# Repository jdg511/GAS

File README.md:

# The Great American Spring

JUCE 7 audio effect by Illicit Apothecary.

Release v2.5 defines the GAS fork from the former Stereo Crossfeed Convolver project. It packages only the four final spring tank IR files:

- `GBS-L.wav`
- `GBS-R.wav`
- `GAS-L.wav`
- `GAS-R.wav`

The plugin provides Main Tanks, optional Ext Reverb Tanks in series or parallel, a constant-sum stereo crossfade, FilterClipper, feedback phase control, mono source handling, and wet/dry output mixing.

## Hardware Mapping Notes

For the real device, the simulation's `predelay + convolution IR` stage should be treated as the software stand-in for a physical spring reverb tank.

- Primary tank simulation: both channels represent `4AB1C1B` tanks.
- Secondary tank simulation: left channel represents a `9EB2C1B` tank and right channel represents a `9EB3C1B` tank.

This means the current JUCE simulation is not just a generic convolution reverb. Its timing and IR choices are standing in for the mechanical behavior of the spring tanks we intend to use in hardware.
Only the predelay and convolution portions are simulation-only. They exist to emulate the behavior of the real spring tanks; the rest of the signal path should be treated as candidate hardware behavior unless we explicitly decide otherwise later.

## Hardware Platform Constraints

The real-world unit should be designed as primarily analog hardware:

- Use passive components, solid-state transistors, and analog / mixed-signal ICs as the main building blocks.
- Do not base the PCB design on an MCU, Arduino, Raspberry Pi, or other general-purpose embedded computer.
- The production hardware should replace the simulation-only predelay and convolution stages with real spring tanks and supporting analog electronics, not runtime convolution or software processing on the PCB.

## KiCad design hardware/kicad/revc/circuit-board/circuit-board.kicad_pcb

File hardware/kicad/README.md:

# KiCad Workspace

KiCad 10 is installed locally on this machine.

This folder is the intended home for the hardware project once schematic capture starts.

## Planned Contents

- `GAS-Hardware.kicad_pro`
- `GAS-Hardware.kicad_sch`
- one schematic file scaffold per board
- board layouts for:
  - input-output
  - tank-driver-recovery
  - ext-tank-routing
  - crossfade-feedback-wet-summing
  - filter-clipper

## Current Status

The KiCad project now has a **real top-level hierarchical shell**, first-pass real symbol capture across every rev-A child sheet, and a first-pass electrically assigned power/backplane page.

What currently exists:

- file naming
- top-level sheet ownership and page ordering
- title blocks
- top-level system notes
- child-sheet interface labels for global rails, I/O boundary nets, inter-board audio nets, and frozen control nets
- first-pass symbol population on every rev-A board sheet
- first-pass DC-entry, rail-generation, and harness-fanout net assignment on `power-backplane.kicad_sch`
- PCB placement scaffold files for all six rev-A boards, generated from the documented board envelope assumptions
- DRC-clean placement scaffolds with four M3 mounting holes plus all currently assigned schematic footprints per board
- capture sequencing
- validated CLI export workflow
- a manifest-driven audit script for measuring schematic population progress

What does **not** yet exist:

- real inter-sheet and intra-sheet pin-level wiring on the five audio/control sheets
- clean ERC after the new symbol-only capture phase
- finished footprint assignment inside every schematic page
- routed copper, zones, final component placement, or Gerber/drill fabrication exports for the PCB files

Capture should now key off:

- [rev-a-schematic-packets.md](C:/Users/Jason/GAS-build/repo/hardware/rev-a-schematic-packets.md:1)
- [rev-a-electrical-capture-worksheet.md](C:/Users/Jason/GAS-build/repo/hardware/rev-a-electrical-capture-worksheet.md:1)
- [rev-a-io-schematic-ready-definition.md](C:/Users/Jason/GAS-build/repo/hardware/rev-a-io-schematic-ready-definition.md:1)
- [rev-a-ext-routing-schematic-ready-definition.md](C:/Users/Jason/GAS-build/repo/hardware/rev-a-ext-routing-schematic-ready-definition.md:1)
- [rev-a-tank-driver-recovery-schematic-ready-definition.md](C:/Users/Jason/GAS-build/repo/hardware/rev-a-tank-driver-recovery-schematic-ready-definition.md:1)
- [rev-a-crossfade-feedback-wet-schematic-ready-definition.md](C:/Users/Jason/GAS-build/repo/hardware/rev-a-crossfade-feedback-wet-schematic-ready-definition.md:1)
- [rev-a-filter-clipper-schematic-ready-definition.md](C:/Users/Jason/GAS-build/repo/hardware/rev-a-filter-clipper-schematic-ready-definition.md:1)
- [rev-a-control-backplane-schematic-ready-definition.md](C:/Users/Jason/GAS-build/repo/hardware/rev-a-control-backplane-schematic-ready-definition.md:1)
- [rev-a-interconnect-pin-map.md](C:/Users/Jason/GAS-build/repo/hardware/rev-a-interconnect-pin-map.md:1)
- [rev-a-bringup-sequence.md](C:/Users/Jason/GAS-build/repo/hardware/rev-a-bringup-sequence.md:1)
- [rev-a-sheet-population-plan.md](C:/Users/Jason/GAS-build/repo/hardware/kicad/rev-a-sheet-population-plan.md:1)
- [rev-a-symbol-manifest.csv](C:/Users/Jason/GAS-build/repo/hardware/kicad/rev-a-symbol-manifest.csv:1)
- [rev-a-net-label-manifest.csv](C:/Users/Jason/GAS-build/repo/hardware/kicad/rev-a-net-label-manifest.csv:1)

## Verification

During this session, the hierarchical top-level shell and all child sheets were accepted by `kicad-cli`, and the release-export script still produced schematic PDFs successfully after the interface-label pass.

Important current nuance:

- symbol population is intentionally ahead of real wire placement
- `kicad-cli sch export pdf` still succeeds
- top-level ERC is no longer clean at this intermediate stage because the hierarchical labels are not yet attached to real wires or symbols
- the current ERC result is therefore a **known intermediate failure**, not a claim that the capture is electrically complete

Current exported folder:

- the historical placeholder export artifact still exists as a file named `hardware/kicad/exports`

Repeatable release/export helper:

- [export-rev-a-release.ps1](C:/Users/Jason/GAS-build/repo/hardware/kicad/export-rev-a-release.ps1:1)
- [rev-a-release-manifest.csv](C:/Users/Jason/GAS-build/repo/hardware/kicad/rev-a-release-manifest.csv:1)

Repeatable capture-progress audit:

- [audit-rev-a-capture.py](C:/Users/Jason/GAS-build/repo/hardware/kicad/audit-rev-a-capture.py:1)
- [rev-a-capture-audit.md](C:/Users/Jason/GAS-build/repo/hardware/kicad/rev-a-capture-audit.md:1)

Run:

```powershell
python hardware/kicad/audit-rev-a-capture.py
```

Current baseline from the latest `2026-06-29` audit:

- top-level hierarchy: `6 / 6` child sheets present
- populated schematic refs: `88 / 88`
- explicit manifest net labels: `82 / 82`

Current release-export / ERC baseline from the same session:

- capture audit: `88 / 88` planned refs present and `82 / 82` manifest labels present
- top-level ERC: `650` known intermediate violations after the I/O-board center-short cleanup pass on `2026-06-29`
- the I/O child sheet dropped from `404` to `376` local violations in the same pass, and its multiple-net-name collisions dropped from `8` to `2`
- the remaining I/O multiple-net-name warnings are the intentional `WD_L_LO <-> WET_SUM_L` and `WD_R_LO <-> WET_SUM_R` wet-return aliases
- the remaining ERC debt is still dominated by top-level unconnected sheet pins, placeholder wire endpoints, off-grid legacy symbol endpoints, and still-unwired child-sheet labels on the non-power sheets
- the power/backplane page itself still stands as the most electrically assigned sheet, but it is not yet the final ripple-decoupling or chassis-bond implementation

Current PCB scaffold baseline:

- `crossfade-feedback-wet.kicad_pcb`: `100 mm x 70 mm`, 8 electrical footprints, 4x M3 mounting holes, DRC clean
- `ext-tank-routing.kicad_pcb`: `120 mm x 80 mm`, 12 electrical footprints, 4x M3 mounting holes, DRC clean
- `filter-clipper.kicad_pcb`: `140 mm x 90 mm`, 19 electrical footprints, 4x M3 mounting holes, DRC clean
- `io-board.kicad_pcb`: `160 mm x 75 mm`, 50 electrical footprints, 4x M3 mounting holes, DRC clean
- `power-backplane.kicad_pcb`: `150 mm x 95 mm`, 14 electrical footprints, 4x M3 mounting holes, DRC clean
- `tank-driver-recovery.kicad_pcb`: `170 mm x 110 mm`, 11 electrical footprints, 4x M3 mounting holes, DRC clean
- these are **placement scaffolds only** and are not routed fabrication outputs

Repeatable PCB footprint placement helper:

- [place-rev-a-board-footprints.py](C:/Users/Jason/GAS-build/repo/hardware/kicad/place-rev-a-board-footprints.py:1)

Current scripted output root:

- `hardware/kicad/release-exports/rev-a-release`

## Order Readiness Gate

Before ordering boards, run:

```powershell
.\hardware\kicad\test-rev-a-order-readiness.ps1
```

The gate writes:

- [rev-a-order-readiness.md](C:/Users/Jason/GAS-build/repo/hardware/kicad/rev-a-order-readiness.md:1)
- [GAS-Hardware-erc-current.json](C:/Users/Jason/GAS-build/repo/hardware/kicad/GAS-Hardware-erc-current.json:1)

It intentionally fails while any of these are true:

- no `*.kicad_pcb` board layout files exist
- top-level ERC has violations
- non-virtual schematic symbols have empty footprint fields
- KiCad/SPICE simulation model properties are absent

The current project is therefore **not order-ready**. It remains in schematic-capture cleanup before PCB layout, DRC, Gerber/drill export, and simulation setup.

## Planned Export Set

- fabrication Gerbers
- drill files
- schematic PDFs
- `BOM.csv`
- centroid / position files
- assembly drawings
- bring-up and calibration notes

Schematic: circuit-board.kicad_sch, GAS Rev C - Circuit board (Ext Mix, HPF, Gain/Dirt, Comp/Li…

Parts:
C101, C103, C105, C207, C208, C209, C210, C307, C308, C309, C310, C805, C1201, C1202, C1241, C1303, C1304, C1305, C1306, C1307, C1308, C1323, C1324, C1345, C1346: 100nF; C_0603_1608Metric; MPN CL10B104KB8NNNC
C102, C110, C111: 10uF 25V; CP_Elec_5x5.8; MPN UWT1E100MCL1GB
C104: 47uF 16V; CP_Elec_6.3x7.7; MPN EEE-FK1C470P
C201, C211, C220, C301, C311, C320, C1302, C1322: 22pF; C_0603_1608Metric; MPN CL10C220JB8NNNC
C202, C203, C212, C213, C302, C303, C312, C313: 68nF film; C_1210_3225Metric; MPN ECH-U1H683JX5
C204, C214, C304, C314: 15nF film; C_1206_3216Metric; MPN ECH-U1H153JX5
C205, C215, C305, C315: 6.8nF film; C_0805_2012Metric; MPN ECH-U1H682JX5
C801, C804, C901, C904, C1301, C1321, C1341, C1342, C1344: 1uF film; C_Rect_L7.2mm_W4.5mm_P5.00mm_FKS2_FKP2_MKS2_MKP2; MPN MKS2C041001F00KSSD
C803, C903: 51pF; C_0603_1608Metric; MPN CL10C510JB8NNNC
C1343: 100pF; C_0603_1608Metric; MPN CL10C101JB8NNNC
D1F, D2F, D3F, D4F, D5F, D801, D802, D901, D902, D1241, D1242, D1341, D1342, D1343: 1N4148W; D_SOD-123; MPN 1N4148W-7-F
D1243: 1N5819HW; D_SOD-123; MPN 1N5819HW-7-F
H1, H2, H3, H4: M3; MountingHole_3.2mm_M3_Pad_Via
K1, K2, K3, K4, K5: G6K-2F-Y DC5; Relay_DPDT_Omron_G6K-2F-Y; MPN G6K-2F-Y DC5
P1: TANK-RET (from tank board); JST_XH_B6B-XH-A_1x06_P2.50mm_Vertical; MPN B6B-XH-A(LF)(SN)
P2: WET-OUT (to io-board); JST_XH_B3B-XH-A_1x03_P2.50mm_Vertical; MPN B3B-XH-A(LF)(SN)
P3: FB-RET (to tank board); JST_XH_B3B-XH-A_1x03_P2.50mm_Vertical; MPN B3B-XH-A(LF)(SN)
P4: PWR (from power board); JST_VH_B4P-VH_1x04_P3.96mm_Vertical; MPN B4P-VH(LF)(SN)
P5: CTL-A: HPF quad 50k lin (PTD904-2015K-B503) on it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; JST_XH_B8B-XH-A_1x08_P2.50mm_Vertical; MPN B8B-XH-A(LF)(SN)
P6: CTL-B: LPF quad 50k lin (PTD904-2015K-B503) on it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; JST_XH_B8B-XH-A_1x08_P2.50mm_Vertical; MPN B8B-XH-A(LF)(SN)
P7: CTL-C: Ext Mix dual 10k lin, Feedback dual 10k lin; JST_XH_B12B-XH-A_1x12_P2.50mm_Vertical; MPN B12B-XH-A(LF)(SN)
P8: CTL-D: switch lines (from control deck); JST_XH_B7B-XH-A_1x07_P2.50mm_Vertical; MPN B7B-XH-A(LF)(SN)
P9: CTL-E: Gain dual 10k lin (control deck P4); JST_XH_B6B-XH-A_1x06_P2.50mm_Vertical; MPN B6B-XH-A(LF)(SN)
Q1201, Q1221: MMBF5457; SOT-23; MPN MMBF5457
Q1341: MMBT3906; SOT-23; MPN MMBT3906-7-F
R60, R61, R62, R63, R64, R101, R102, R207, R213, R236, R307, R313, R336, R1208, R1228, R1244, R1245, R1343, R1344, R1345, R1346, R1348, R1351, R1357: 10k; R_0603_1608Metric; MPN RC0603FR-0710KL
R201, R202, R301, R302: 1.43k; R_0603_1608Metric; MPN RC0603FR-071K43L
R203, R208, R234, R303, R308, R334, R1203, R1204, R1223, R1224: 1M; R_0603_1608Metric; MPN RC0603FR-071ML
R204, R205, R209, R210, R304, R305, R309, R310: 499R; R_0603_1608Metric; MPN RC0603FR-07499RL
R206, R306: 5.9k; R_0603_1608Metric; MPN RC0603FR-075K9L
R211, R220, R221, R222, R223, R224, R311, R320, R321, R322, R323, R324, R801, R804, R901, R904, R1206, R1207, R1226, R1227, R1350, R1353, R1355, R1356: 100k; R_0603_1608Metric; MPN RC0603FR-07100KL
R212, R312: 15.8k; R_0603_1608Metric; MPN RC0603FR-0715K8L
R214, R230, R233, R314, R330, R333: 100R; R_0603_1608Metric; MPN RC0603FR-07100RL
R215, R315, R1205, R1225: 47k; R_0603_1608Metric; MPN RC0603FR-0747KL
R216, R316: 680R; R_0603_1608Metric; MPN RC0603FR-07680RL
R231, R232, R331, R332, R1241, R1242, R1301, R1302, R1303, R1304, R1321, R1322, R1323, R1324, R1341, R1342, R1347, R1349: 20k; R_0603_1608Metric; MPN RC0603FR-0720KL
R235, R335: 59k; R_0603_1608Metric; MPN RC0603FR-0759KL
R802, R902: 4.7k; R_0603_1608Metric; MPN RC0603FR-074K7L
R803, R903: 51k; R_0603_1608Metric; MPN RC0603FR-0751KL
R1201, R1221: 22k; R_0603_1608Metric; MPN RC0603FR-0722KL
R1202, R1222: 2.2k; R_0603_1608Metric; MPN RC0603FR-072K2L
R1243: 40.2k; R_0603_1608Metric; MPN RC0603FR-0740K2L
R1246: 1.5k; R_0603_1608Metric; MPN RC0603FR-071K5L
R1247: 2.2M; R_0603_1608Metric; MPN RC0603FR-072M2L
R1305, R1325: 150k; R_0603_1608Metric; MPN RC0603FR-07150KL
R1306, R1326: 5.1k; R_0603_1608Metric; MPN RC0603FR-075K1L
R1352: 182k; R_0603_1608Metric; MPN RC0603FR-07182KL
R1354: 1.82M; R_0603_1608Metric; MPN RC0603FR-071M82L
RV1201, RV1221, RV1342: 10k; Potentiometer_Bourns_3314J_Vertical; MPN 3314J-1-103E
RV1301, RV1321: 50k; Potentiometer_Bourns_3314J_Vertical; MPN 3314J-1-503E
U101: L78L09; SOT-89-3; MPN L78L09ACUTR
U102, U402: TL072HIDR; SOIC-8_3.9x4.9mm_P1.27mm; MPN TL072HIDR
U201, U202, U301, U302, U1201, U1301, U1302, U1305: OPA1679IDR; SOIC-14_3.9x8.7mm_P1.27mm; MPN OPA1679IDR
U1303, U1304: V2181; SIP-8_19x3mm_P2.54mm; MPN V2181

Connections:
+5VAUX: P4.4, P8.6
+9VC: C102.1, C103.1, C105.1, C805.1, R101.1, U101.1 (OUT), U102.8 (V+), U402.8 (V+)
+15VA: C101.1, C110.1, C207.1, C209.1, C307.1, C309.1, C1201.1, C1303.1, C1305.1, C1307.1, C1323.1, C1345.1, P4.1, R1355.1, RV1301.1, RV1321.1, U101.3 (IN), U201.4 (V+), U202.4 (V+), U301.4 (V+), U302.4 (V+), U1201.4 (V+), U1301.4 (V+), U1302.4 (V+), U1303.7 (V+), U1304.7 (V+), U1305.4 (V+)
-15VA: C111.2, C208.2, C210.2, C308.2, C310.2, C1202.2, C1304.2, C1306.2, C1308.2, C1324.2, C1346.2, P4.3, R1306.2, R1326.2, R1356.2, RV1201.1, RV1221.1, RV1301.3, RV1321.3, U201.11 (V-), U202.11 (V-), U301.11 (V-), U302.11 (V-), U1201.11 (V-), U1301.11 (V-), U1302.11 (V-), U1305.11 (V-)
AGND: C101.2, C102.2, C103.2, C104.2, C105.2, C110.2, C111.1, C205.2, C207.2, C208.1, C209.2, C210.1, C215.2, C305.2, C307.2, C308.1, C309.2, C310.1, C315.2, C805.2, C1201.2, C1202.1, C1241.2, C1303.2, C1304.1, C1305.2, C1306.1, C1307.2, C1308.1, C1323.2, C1324.1, C1344.2, C1345.2, C1346.1, D1F.2 (A), D2F.2 (A), D3F.2 (A), D4F.2 (A), D5F.2 (A), H1.1, H2.1, H3.1, H4.1, K1.8, K2.8, K3.8, K4.8, K5.8, P1.2, P1.5, P2.2, P3.2, P4.2, P5.3, P5.7, P7.3, P7.6, P7.9, P7.12, P8.7, Q1201.2 (S), Q1221.2 (S), Q1341.1 (B), R60.2, R61.2, R62.2, R63.2, R64.2, R102.2, R207.2, R208.2, R211.2, R216.2, R223.2, R224.2, R234.2, R236.2, R307.2, R308.2, R311.2, R316.2, R323.2, R324.2, R334.2, R336.2, R804.2, R904.2, R1202.2, R1208.2, R1222.2, R1228.2, R1247.2, R1352.2, R1357.2, RV1201.3, RV1221.3, U101.2 (GND), U102.4 (V-), U102.5 (+), U201.3 (+), U201.10 (+), U202.3 (+), U202.12 (+), U301.3 (+), U301.10 (+), U302.3 (+), U302.12 (+), U402.4 (V-), U1201.10 (+), U1201.12 (+), U1301.3 (+), U1301.5 (+), U1301.10 (+), U1301.12 (+), U1303.2 (EC+), U1303.6 (GND), U1304.2 (EC+), U1304.6 (GND), U1305.3 (+), U1305.5 (+), U1305.10 (+), U1305.12 (+)
BUS_L: K3.3, R209.1, R211.1
BUS_R: K3.6, R309.1, R311.1
CL_OP: D1341.2 (A), U1302.7
CTL_COMP: D2F.1 (K), K2.1, P8.2, R61.1
CTL_DIRT: D1F.1 (K), K1.1, P8.1, R60.1
CTL_FB_INV: D4F.1 (K), K4.1, P8.5, R63.1
CTL_LIMIT: D3F.1 (K), K3.1, P8.3, R62.1
CTL_MEGA: D5F.1 (K), K5.1, P8.4, R64.1
DET_AVG: C1344.1, R1346.2, R1350.1
DET_C_L: C1341.2, R1341.1
DET_C_R: C1342.2, R1342.1
DET_OUT: C1343.2, Q1341.2 (E), R1351.1, U1305.14
DET_SUM: R1343.2, R1344.1, R1347.1, U1305.1
DET_SUM_N: R1341.2, R1342.2, R1343.1, U1305.2 (-)
DYN_IN_L: K1.3, K2.2, R1201.1, R1301.1
DYN_IN_R: K1.6, K2.7, R1221.1, R1321.1
DYN_MID_L: K2.3, K3.2
DYN_MID_R: K2.6, K3.7
EXM_L_W: P7.2, R221.1
EXM_R_W: P7.5, R321.1
FBI_N_L: R231.2, R232.1, U202.13 (-)
FBI_N_R: R331.2, R332.1, U302.13 (-)
FBP_L_W: P7.8, R234.1, U202.10 (+)
FBP_R_W: P7.11, R334.1, U302.10 (+)
FB_BUF_L: K4.2, R231.1, U202.8, U202.9 (-)
FB_BUF_R: K4.7, R331.1, U302.8, U302.9 (-)
FB_INV_L: K4.4, R232.2, U202.14
FB_INV_R: K4.5, R332.2, U302.14
FB_RAW_L: K5.3, R233.1
FB_RAW_R: K5.6, R333.1
FB_RET_L: P3.1, R233.2
FB_RET_R: P3.3, R333.2
FB_SEL_L: K4.3, K5.2, K5.5
FB_SEL_R: K4.6, K5.4, K5.7
FET_BIAS_L: R1205.2, RV1201.2
FET_BIAS_R: R1225.2, RV1221.2
FET_CV_L: R1203.2, R1205.1, R1206.1
FET_CV_R: R1223.2, R1225.1, R1226.1
FET_DIV_L: Q1201.1 (D), R1201.2, R1202.1, R1204.2, U1201.3 (+)
FET_DIV_R: Q1221.1 (D), R1221.2, R1222.1, R1224.2, U1201.5 (+)
FET_G_L: Q1201.3 (G), R1203.1, R1204.1
FET_G_R: Q1221.3 (G), R1223.1, R1224.1
FET_MK_L: R1207.2, R1208.1, U1201.2 (-)
FET_MK_R: R1227.2, R1228.1, U1201.6 (-)
FET_OUT_L: K2.4, R1207.1, R1241.1, U1201.1
FET_OUT_R: K2.5, R1227.1, R1242.1, U1201.7
FET_SC: R1206.2, R1226.2, U1302.8, U1302.9 (-)
FW_N: R1347.2, R1348.2, R1349.1, U1305.9 (-)
FW_OUT: R1346.1, R1349.2, U1305.8
GAIN_L_HI: P9.1, R201.2
GAIN_L_LO: P9.3, R202.1
GAIN_L_W: C201.1, P9.2, R203.1, U201.9 (-)
GAIN_OUT_L: C201.2, K1.2, R202.2, R203.2, R215.1, U201.8
GAIN_OUT_R: C301.2, K1.7, R302.2, R303.2, R315.1, U301.8
GAIN_R_HI: P9.4, R301.2
GAIN_R_LO: P9.6, R302.1
GAIN_R_W: C301.1, P9.5, R303.1, U301.9 (-)
HPF_FB_L: R206.2, R207.1, U201.6 (-)
HPF_FB_R: R306.2, R307.1, U301.6 (-)
HPF_L1_W: P5.2, R204.2
HPF_L2_W: P5.4, R205.2
HPF_N1_L: C202.2, C203.1, C212.2, C213.1, R204.1
HPF_N1_R: C302.2, C303.1, C312.2, C313.1, R304.1
HPF_OUT_L: P5.1, R201.1, R206.1, U201.7
HPF_OUT_R: P5.5, R301.1, R306.1, U301.7
HPF_P_L: C203.2, C213.2, R205.1, R208.1, U201.5 (+)
HPF_P_R: C303.2, C313.2, R305.1, R308.1, U301.5 (+)
HPF_R1_W: P5.6, R304.2
HPF_R2_W: P5.8, R305.2
HW_N: D1342.2 (A), R1344.2, R1345.2, U1305.6 (-)
HW_OP: D1342.1 (K), D1343.2 (A), U1305.7
HW_X: D1343.1 (K), R1345.1, R1348.1
LOG_N: C1343.1, Q1341.3 (C), R1350.2, U1305.13 (-)
LPF_L1_W: P6.2, R209.2
LPF_L2_W: P6.4, R210.2
LPF_N1_L: C204.1, C214.1, P6.1, R210.1
LPF_N1_R: C304.1, C314.1, P6.5, R310.1
LPF_OUT_L: C204.2, C214.2, R212.1, U201.13 (-), U201.14
LPF_OUT_R: C304.2, C314.2, R312.1, U301.13 (-), U301.14
LPF_P_L: C205.1, C215.1, P6.3, U201.12 (+)
LPF_P_R: C305.1, C315.1, P6.7, U301.12 (+)
LPF_R1_W: P6.6, R309.2
LPF_R2_W: P6.8, R310.2
MIX_N_L: C220.1, R220.2, R221.2, R222.1, U201.2 (-)
MIX_N_R: C320.1, R320.2, R321.2, R322.1, U301.2 (-)
OB_N_L: C211.1, R212.2, R213.1, U202.2 (-)
OB_N_R: C311.1, R312.2, R313.1, U302.2 (-)
PAD_L: C801.1, R215.2, R216.1
PAD_R: C901.1, R315.2, R316.1
PRI_RET_L: P1.1, R220.1, R223.1
PRI_RET_R: P1.3, R320.1, R323.1
SC2_ENV: C1241.1, R1246.2, R1247.1, U1302.10 (+)
SC2_N: R1241.2, R1242.2, R1243.1, U1201.9 (-)
SC2_OP: D1241.1 (K), D1242.2 (A), U1201.14
SC2_PK: D1243.1 (K), R1246.1
SC2_RN: D1241.2 (A), R1244.2, R1245.2, U1201.13 (-)
SC2_SUM: R1243.2, R1244.1, U1201.8
SC2_X: D1242.1 (K), D1243.2 (A), R1245.1
SEC_BUF_L: P7.1, R230.2
SEC_BUF_R: P7.4, R330.2
SEC_RET_L: P1.4, R224.1, R230.1
SEC_RET_R: P1.6, R324.1, R330.1
SPARE_U102_2: U102.6 (-), U102.7
TANK_MIX_L: C202.1, C212.1, C220.2, R222.2, U201.1
TANK_MIX_R: C302.1, C312.1, C320.2, R322.2, U301.1
TH_BOT: R1356.1, RV1342.3
TH_N: R1353.2, R1354.1, U1302.2 (-)
TH_OUT: R1354.2, U1302.1, U1302.5 (+)
TH_P: R1351.2, R1352.1, U1302.3 (+)
TH_REF: R1353.1, RV1342.2
TH_TOP: R1355.2, RV1342.1
TS_CLIP_L: C803.1, C804.1, D801.1 (K), D802.2 (A), R803.1, U402.1
TS_CLIP_R: C903.1, C904.1, D901.1 (K), D902.2 (A), R903.1, U402.7
TS_DIV_L: C804.2, R804.1, U202.5 (+)
TS_DIV_R: C904.2, R904.1, U302.5 (+)
TS_FB2_L: R235.2, R236.1, U202.6 (-)
TS_FB2_R: R335.2, R336.1, U302.6 (-)
TS_FB_L: C803.2, D801.2 (A), D802.1 (K), R802.1, R803.2, U402.2 (-)
TS_FB_R: C903.2, D901.2 (A), D902.1 (K), R902.1, R903.2, U402.6 (-)
TS_IN_L: C801.2, R801.1, U402.3 (+)
TS_IN_R: C901.2, R901.1, U402.5 (+)
TS_OUT_L: K1.4, R235.1, U202.7
TS_OUT_R: K1.5, R335.1, U302.7
VBIAS: R801.2, R802.2, R901.2, R902.2, U102.1, U102.2 (-)
VB_RAW: C104.1, R101.2, R102.1, U102.3 (+)
VCA_C_L: C1301.2, R1303.1
VCA_C_R: C1321.2, R1323.1
VCA_EC: U1302.13 (-), U1302.14, U1303.3 (EC-), U1304.3 (EC-)
VCA_EC_RAW: D1341.1 (K), R1357.1, U1302.6 (-), U1302.12 (+)
VCA_INV_L: C1301.1, R1302.2, U1301.1
VCA_INV_R: C1321.1, R1322.2, U1301.8
VCA_IN_L: R1303.2, U1303.1 (IN)
VCA_IN_N_L: R1301.2, R1302.1, U1301.2 (-)
VCA_IN_N_R: R1321.2, R1322.1, U1301.9 (-)
VCA_IN_R: R1323.2, U1304.1 (IN)
VCA_OUT_L: C1302.2, C1341.1, K3.4, R1304.2, U1301.7
VCA_OUT_R: C1322.2, C1342.1, K3.5, R1324.2, U1301.14
VCA_O_L: C1302.1, R1304.1, U1301.6 (-), U1303.8 (OUT)
VCA_O_R: C1322.1, R1324.1, U1301.13 (-), U1304.8 (OUT)
VCA_SYMW_L: R1305.1, RV1301.2
VCA_SYMW_R: R1325.1, RV1321.2
VCA_SYM_L: R1305.2, U1303.4 (SYM)
VCA_SYM_R: R1325.2, U1304.4 (SYM)
VCA_VN_L: R1306.1, U1303.5 (V-/ISET)
VCA_VN_R: R1326.1, U1304.5 (V-/ISET)
WET_L: P2.1, R214.2
WET_R: P2.3, R314.2
WET_RAW_L: C211.2, P7.7, R213.2, R214.1, U202.1
WET_RAW_R: C311.2, P7.10, R313.2, R314.1, U302.1

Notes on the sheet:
Connectors
Mechanical
Power, +9VC, VBIAS
Main path L: Ext Mix sum, HPF, Gain, LPF
Output, feedback, make-ups L
Tube Screamer L: Rf 51k / Rg 4.7k, 1N4148W pair, +9VC
Main path R: Ext Mix sum, HPF, Gain, LPF
Output, feedback, make-ups R
Tube Screamer R: Rf 51k / Rg 4.7k, 1N4148W pair, +9VC
Comp: MMBF5457 FET compressor (1176 territory), linked feedback sidechain
Limit: Coolaudio V2181 VCA x2 (THAT 2181 pin-compatible), discrete log-average detector (feedback), 10:1
Limit detector + threshold
Relays: Dirt, Comp, Limit, FB phase, MEGAVERB (Omron G6K-2F-Y 5 V)
Power flags

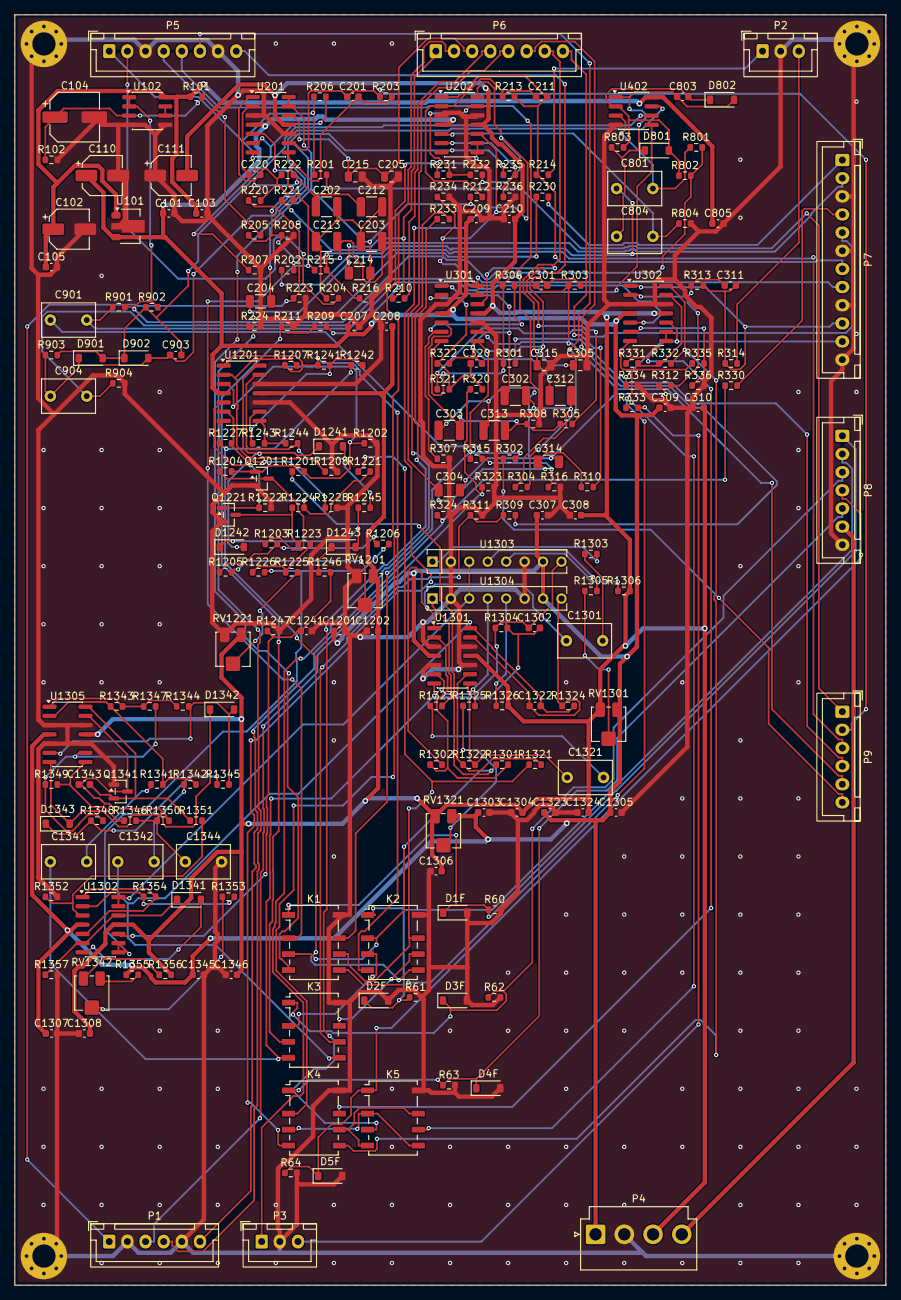
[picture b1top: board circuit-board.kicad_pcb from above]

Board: 2 copper layers, 120.0 x 175.0 mm, 242 parts (0 on the bottom side), 154 nets.

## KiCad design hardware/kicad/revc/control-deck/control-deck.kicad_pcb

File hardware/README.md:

# GAS Hardware Build

This folder is the starting point for turning the JUCE spring-reverb simulation into a real analog product.

## Core Constraints

- The real unit is primarily analog.
- Use passive parts, transistors, and analog or mixed-signal ICs.
- Do not use an MCU, Arduino, Raspberry Pi, or other general-purpose embedded computer on the production PCB.
- The external audio interfaces should be balanced line level, nominally `+4 dBu`, with 600-ohm capable line I/O behavior.
- The external audio connectors should be combo `XLR / TRS` jacks.
- The enclosure format is now a **user-supplied cylindrical tube**, `10 in` nominal diameter (standard pipe/cap size; `9 in` fits but is rarely stocked) and about `48 in` long.
- All external audio connections and DC power entry should land on **one circular service endcap**, in the spirit of the original Great British Spring.
- In the audio path, avoid ceramic, tantalum, and electrolytic capacitors wherever practical; prefer film-based or other non-ceramic/non-electrolytic solutions and use direct coupling where it makes sense. Power-supply and rail-decoupling positions may use ceramics or electrolytics when practical.
- Only the simulation's predelay and convolution blocks are software-only stand-ins for the real spring tanks.
- The real hardware should use the target tanks directly:
  - Primary tanks: `4AB1C1B` left and `4AB1C1B` right
  - Secondary tanks: `9EB2C1B` left and `9EB3C1B` right
- Plan around `+15VA / -15VA`, but prefer parts that can tolerate at least `+18V / -18V` wherever practical.
- Mains conversion lives in an **external `+24 VDC` wall-adapter strategy** (`750 mA / 18 W`, Triad Magnetics `WSU240-0750` regulated SMPS from DigiKey, selected `2026-07-04`). The chassis takes DC at a barrel jack and generates `+15V / -15V / +5V` on-board from that single DC input. No mains-side circuitry inside the enclosure. The Triad unit is a regulated SMPS; the P-0 receiving check in [rev-a-external-dc-power.md](rev-a-external-dc-power.md) still applies at first power-up.

## Board Roadmap

We are partitioning the product into analog boards so each section can be designed, tested, and revised independently.

1. Input / Output board
   - Balanced line receiver, dry split, final wet/dry summing, balanced line driver
2. Ext Reverb Tanks Off / Series / Parallel board
   - Secondary tank routing and amount control
3. Filter and Clipping board
   - Drive, HPF, selectable clipping, LPF
4. Tank Driver / Recovery board
   - Real spring tank send and return electronics for primary and secondary tanks
5. Crossfade / Feedback / Mixer board
   - Stereo tank crossfade, feedback loop, phase invert, inter-board summing
6. Power / Control / Interconnect board
   - Analog supply rails, panel controls, board-to-board headers, grounding strategy

## Signal-Path Mapping

The current software path is:

`input -> dry tap + wet path -> tank model -> stereo crossfade -> filter/clipper -> feedback -> wet/dry mix -> output`

The real hardware path should become:

`balanced line receiver -> dry split + wet send -> real tank drive/recovery path -> stereo crossfade -> filter/clipper -> feedback loop -> wet/dry output mixer -> balanced line driver`

The only direct substitution is:

- `predelay + convolution` in software
- replaced by
- real tank drive + real spring tank + recovery stages in hardware

## Design Intent

- Keep the board architecture modular so a third-party PCB house can fabricate repeatable revisions.
- Favor through-hole panel hardware and serviceable connectors where practical.
- Keep the control surface directly analog whenever possible: pots, toggles, rotary switches, relay logic, and analog switch ICs are all acceptable paths.
- Avoid any hardware decision that depends on firmware existing later.

## Build Handoff Entry Points

If you are picking this package up to actually build a unit, start here:

- [rev-a-external-dc-power.md](rev-a-external-dc-power.md) — external wall-adapter power topology and on-board ±15V / +5V generation
- [rev-a-pipe-enclosure-concept.md](rev-a-pipe-enclosure-concept.md) — cylindrical shell, endcap, rail, and tank-mount concept
- [rev-a-endcap-panel-layout.md](rev-a-endcap-panel-layout.md) — service-endcap zoning for combo jacks, DC jack, and controls
- [rev-a-endcap-hole-table.md](rev-a-endcap-hole-table.md) — first drilling/cutout draft for the circular service endcap
- [rev-a-endcap-hole-table.csv](rev-a-endcap-hole-table.csv) — machine-readable companion to the endcap hole table
- [rev-a-board-outline-assumptions.md](rev-a-board-outline-assumptions.md) — target board envelopes and axial placement inside the tube
- [rev-a-board-outline-assumptions.csv](rev-a-board-outline-assumptions.csv) — machine-readable board envelope and station map
- [rev-a-harness-cut-lengths.md](rev-a-harness-cut-lengths.md) — prototype harness cut lengths for boards, tanks, and panel wiring
- [rev-a-harness-cut-lengths.csv](rev-a-harness-cut-lengths.csv) — machine-readable harness-length companion
- [rev-a-board-package-freeze.md](rev-a-board-package-freeze.md) — compact board-by-board freeze for schematic capture and quoting
- [rev-a-electrical-capture-worksheet.md](rev-a-electrical-capture-worksheet.md) — next-pass electrical wiring brief keyed to the actual KiCad refs
- [rev-a-io-schematic-ready-definition.md](rev-a-io-schematic-ready-definition.md) — exact first-pass I/O unit allocation, passive map, and connector/net ownership
- [rev-a-ext-routing-schematic-ready-definition.md](rev-a-ext-routing-schematic-ready-definition.md) — exact first-pass ext-routing relay ownership, control decode, and passive map
- [rev-a-tank-driver-recovery-schematic-ready-definition.md](rev-a-tank-driver-recovery-schematic-ready-definition.md) — exact first-pass tank send/recovery stage ownership, shield strategy, and passive map
- [rev-a-crossfade-feedback-wet-schematic-ready-definition.md](rev-a-crossfade-feedback-wet-schematic-ready-definition.md) — exact first-pass crossfade, wet-return, and feedback-path definition
- [rev-a-filter-clipper-schematic-ready-definition.md](rev-a-filter-clipper-schematic-ready-definition.md) — exact first-pass filter/drive/clip stage ownership and mode truth
- [rev-a-control-backplane-schematic-ready-definition.md](rev-a-control-backplane-schematic-ready-definition.md) — exact first-pass control landing, mode encoding, and backplane reserve policy
- [rev-a-board-connector-schedule.csv](rev-a-board-connector-schedule.csv) — machine-readable connector ownership and harness schedule
- [rev-a-quote-request-packet.md](rev-a-quote-request-packet.md) — exactly which files to send each vendor and template request emails
- [rev-a-total-cost-rollup.md](rev-a-total-cost-rollup.md) — single per-unit cost estimate across electronics, fab, assembly, tanks, enclosure, and labor
- [rev-a-bench-test-procedures.md](rev-a-bench-test-procedures.md) — per-board test procedures with specific signals, equipment, and pass/fail thresholds
- [rev-a-manufacturing.md](rev-a-manufacturing.md) — vendor recommendations and file conventions
- [bom/rev-a-procurement-snapshot.md](bom/rev-a-procurement-snapshot.md) — current exact-part sourcing snapshot and scope split
- [rev-a-bringup-sequence.md](rev-a-bringup-sequence.md) — board-by-board power-up order
- [rev-a-open-issues.md](rev-a-open-issues.md) — what is still genuinely unresolved

## Next Deliverables

- Shared signal naming and connector conventions
- One spec per board
- Schematic packets with stage ownership and pin-level harness maps
- Control-law and circuit-value tables that track the current plugin behavior
- Remaining audio-sheet pin-level

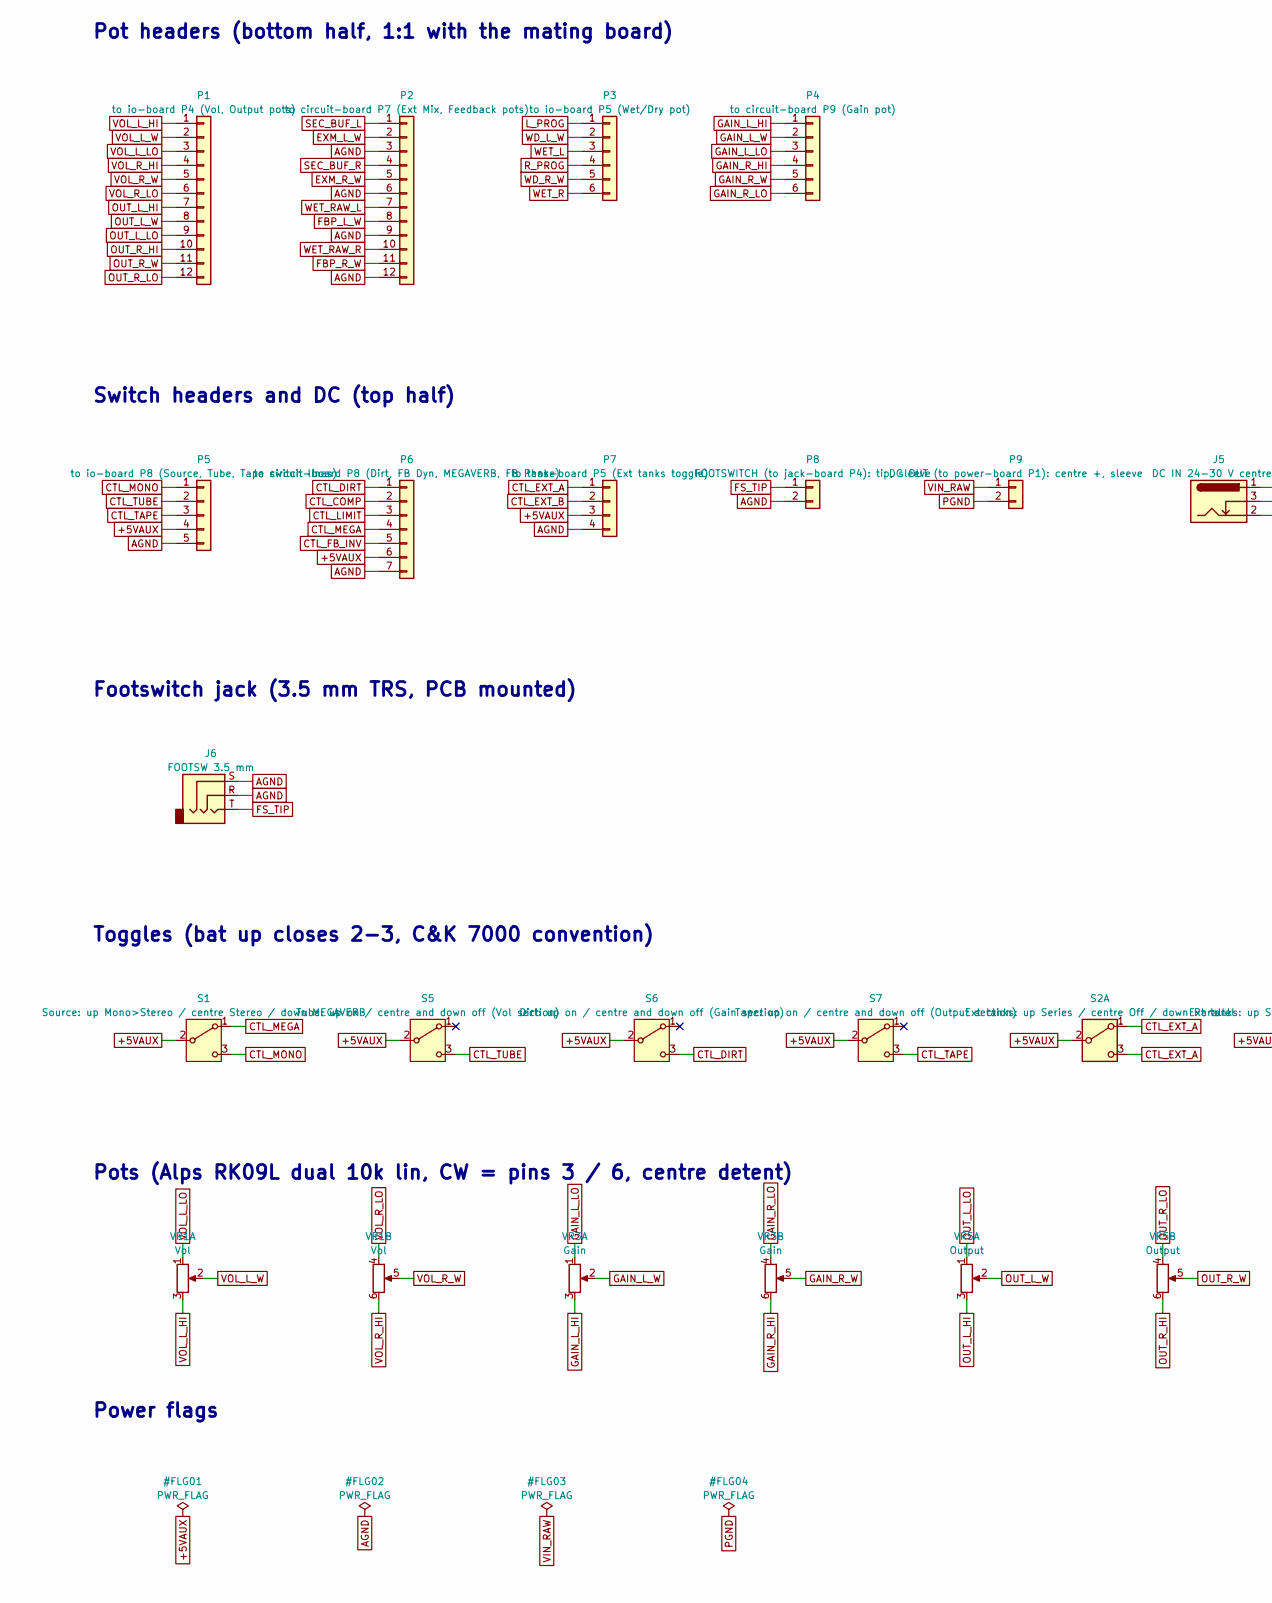
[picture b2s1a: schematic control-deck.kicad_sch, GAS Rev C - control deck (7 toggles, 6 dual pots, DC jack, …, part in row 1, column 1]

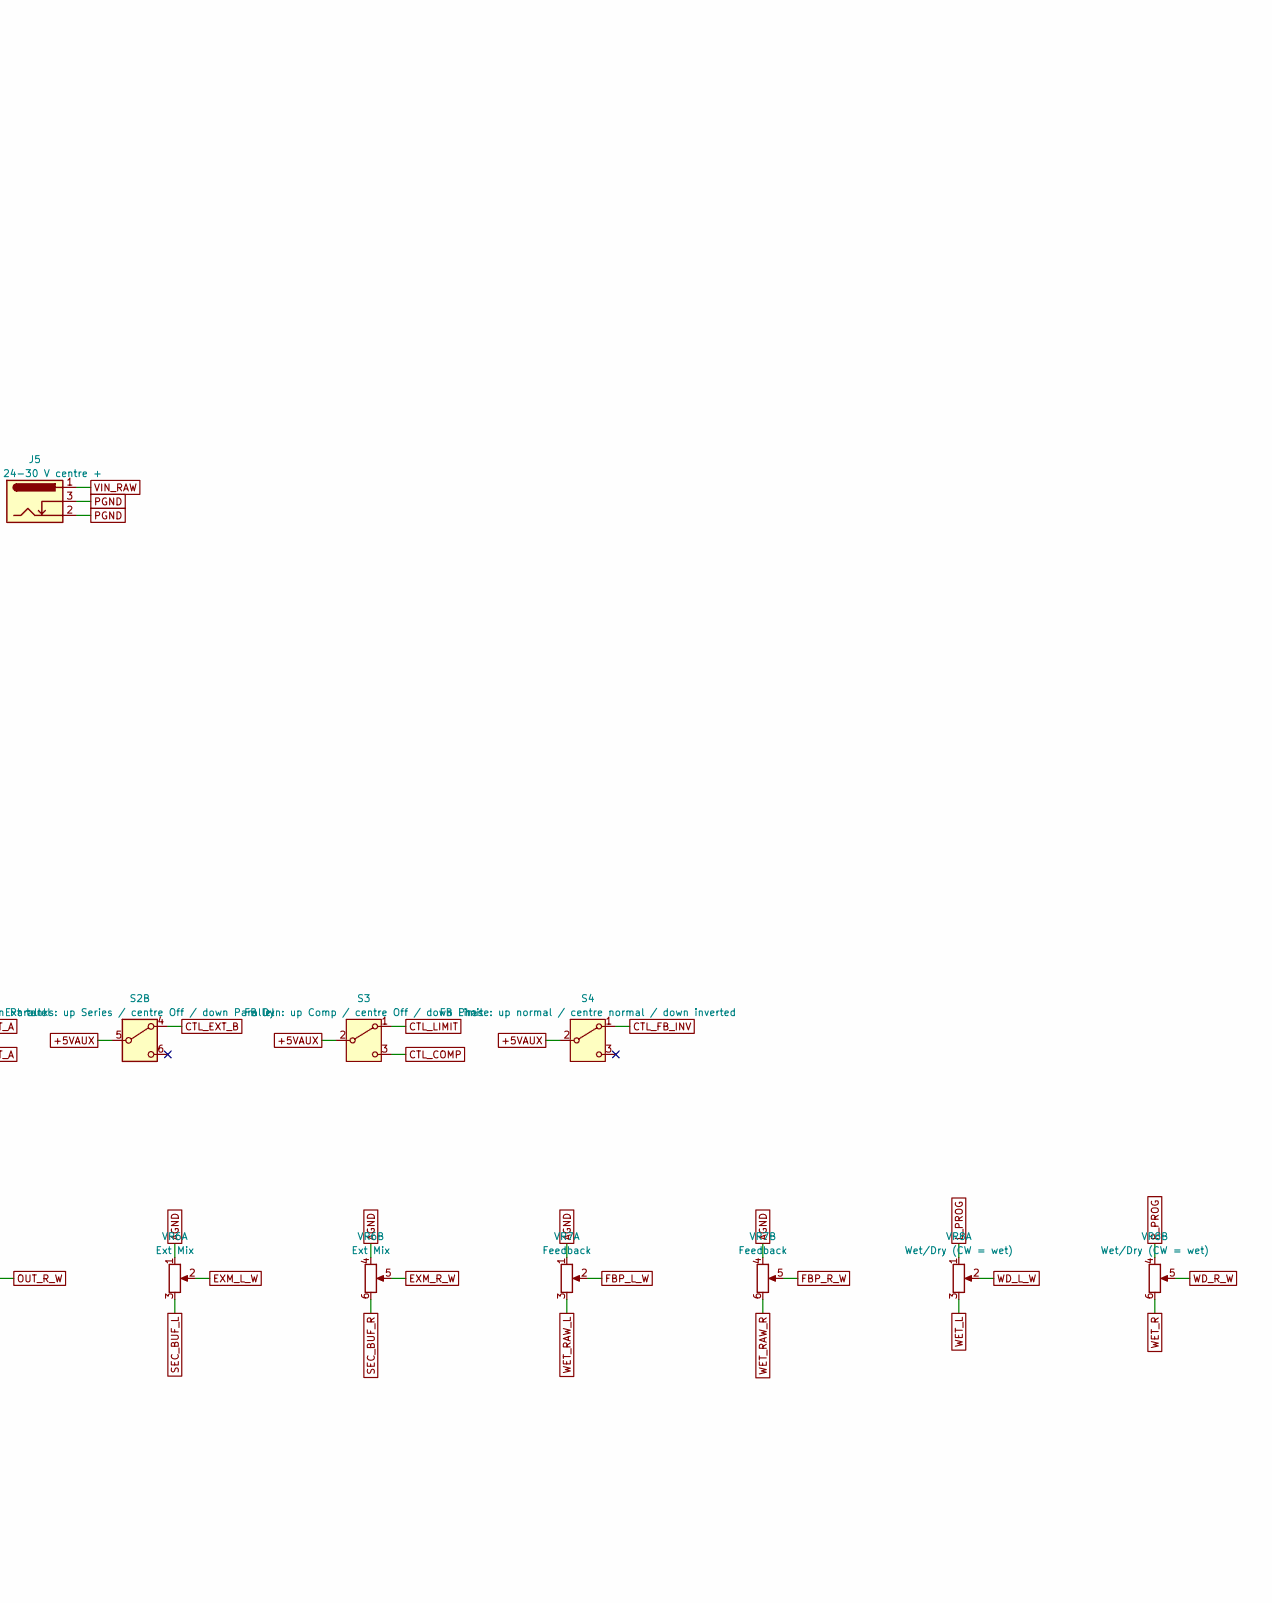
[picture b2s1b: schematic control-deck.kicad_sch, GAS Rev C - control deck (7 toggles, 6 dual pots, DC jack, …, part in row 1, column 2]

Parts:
J5: DC IN 24-30 V centre +; BarrelJack_SameSky_PJ-064B_Vertical; MPN PJ-064B
J6: FOOTSW 3.5 mm; Jack_3.5mm_PJ-301C_Vertical; MPN PJ-301C
P1: to io-board P4 (Vol, Output pots); JST_XH_B12B-XH-A_1x12_P2.50mm_Vertical; MPN B12B-XH-A(LF)(SN)
P2: to circuit-board P7 (Ext Mix, Feedback pots); JST_XH_B12B-XH-A_1x12_P2.50mm_Vertical; MPN B12B-XH-A(LF)(SN)
P3: to io-board P5 (Wet/Dry pot); JST_XH_B6B-XH-A_1x06_P2.50mm_Vertical; MPN B6B-XH-A(LF)(SN)
P4: to circuit-board P9 (Gain pot); JST_XH_B6B-XH-A_1x06_P2.50mm_Vertical; MPN B6B-XH-A(LF)(SN)
P5: to io-board P8 (Source, Tube, Tape switch lines); JST_XH_B5B-XH-A_1x05_P2.50mm_Vertical; MPN B5B-XH-A(LF)(SN)
P6: to circuit-board P8 (Dirt, FB Dyn, MEGAVERB, FB P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; JST_XH_B7B-XH-A_1x07_P2.50mm_Vertical; MPN B7B-XH-A(LF)(SN)
P7: to tank-board P5 (Ext tanks toggle); JST_XH_B4B-XH-A_1x04_P2.50mm_Vertical; MPN B4B-XH-A(LF)(SN)
P8: FOOTSWITCH (to jack-board P4): tip, sleeve; JST_XH_B2B-XH-A_1x02_P2.50mm_Vertical; MPN B2B-XH-A(LF)(SN)
P9: DC OUT (to power-board P1): centre +, sleeve; JST_VH_B2P-VH_1x02_P3.96mm_Vertical; MPN B2P-VH(LF)(SN)
S1: Source: up Mono>Stereo / centre Stereo / down MEG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; SW_Toggle_CK7000_SPDT_PC_Vertical; MPN 1MS3T1B1M2QES-5
S2: Ext tanks: up Series / centre Off / down Parallel; SW_Toggle_CK7000_DPDT_PC_Vertical; MPN 1MD3T1B1M2QES
S3: FB Dyn: up Comp / centre Off / down Limit; SW_Toggle_CK7000_SPDT_PC_Vertical; MPN 1MS3T1B1M2QES-5
S4: FB Phase: up normal / centre normal / down invert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; SW_Toggle_CK7000_SPDT_PC_Vertical; MPN 1MS3T1B1M2QES-5
S5: Tube: up on / centre and down off (Vol section); SW_Toggle_CK7000_SPDT_PC_Vertical; MPN 1MS3T1B1M2QES-5
S6: Dirt: up on / centre and down off (Gain section); SW_Toggle_CK7000_SPDT_PC_Vertical; MPN 1MS3T1B1M2QES-5
S7: Tape: up on / centre and down off (Output section); SW_Toggle_CK7000_SPDT_PC_Vertical; MPN 1MS3T1B1M2QES-5
VR1: Vol; Potentiometer_Alps_RK09L_Double_Vertical; MPN RK09L1240015
VR3: Gain; Potentiometer_Alps_RK09L_Double_Vertical; MPN RK09L1240015
VR5: Output; Potentiometer_Alps_RK09L_Double_Vertical; MPN RK09L1240015
VR6: Ext Mix; Potentiometer_Alps_RK09L_Double_Vertical; MPN RK09L1240015
VR7: Feedback; Potentiometer_Alps_RK09L_Double_Vertical; MPN RK09L1240015
VR8: Wet/Dry (CW = wet); Potentiometer_Alps_RK09L_Double_Vertical; MPN RK09L1240015

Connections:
+5VAUX: P5.4, P6.6, P7.3, S1.2 (B), S2.2 (B), S2.5 (B), S3.2 (B), S4.2 (B), S5.2 (B), S6.2 (B), S7.2 (B)
AGND: J6.R, J6.S, P2.3, P2.6, P2.9, P2.12, P5.5, P6.7, P7.4, P8.2, VR6.1, VR6.4, VR7.1, VR7.4
CTL_COMP: P6.2, S3.3 (C)
CTL_DIRT: P6.1, S6.3 (C)
CTL_EXT_A: P7.1, S2.1 (A), S2.3 (C)
CTL_EXT_B: P7.2, S2.4 (A)
CTL_FB_INV: P6.5, S4.1 (A)
CTL_LIMIT: P6.3, S3.1 (A)
CTL_MEGA: P6.4, S1.1 (A)
CTL_MONO: P5.1, S1.3 (C)
CTL_TAPE: P5.3, S7.3 (C)
CTL_TUBE: P5.2, S5.3 (C)
EXM_L_W: P2.2, VR6.2
EXM_R_W: P2.5, VR6.5
FBP_L_W: P2.8, VR7.2
FBP_R_W: P2.11, VR7.5
FS_TIP: J6.T, P8.1
GAIN_L_HI: P4.1, VR3.3
GAIN_L_LO: P4.3, VR3.1
GAIN_L_W: P4.2, VR3.2
GAIN_R_HI: P4.4, VR3.6
GAIN_R_LO: P4.6, VR3.4
GAIN_R_W: P4.5, VR3.5
L_PROG: P3.1, VR8.1
OUT_L_HI: P1.7, VR5.3
OUT_L_LO: P1.9, VR5.1
OUT_L_W: P1.8, VR5.2
OUT_R_HI: P1.10, VR5.6
OUT_R_LO: P1.12, VR5.4
OUT_R_W: P1.11, VR5.5
PGND: J5.2, J5.3, P9.2
R_PROG: P3.4, VR8.4
SEC_BUF_L: P2.1, VR6.3
SEC_BUF_R: P2.4, VR6.6
VIN_RAW: J5.1, P9.1
VOL_L_HI: P1.1, VR1.3
VOL_L_LO: P1.3, VR1.1
VOL_L_W: P1.2, VR1.2
VOL_R_HI: P1.4, VR1.6
VOL_R_LO: P1.6, VR1.4
VOL_R_W: P1.5, VR1.5
WD_L_W: P3.2, VR8.2
WD_R_W: P3.5, VR8.5
WET_L: P3.3, VR8.3
WET_R: P3.6, VR8.6
WET_RAW_L: P2.7, VR7.3
WET_RAW_R: P2.10, VR7.6

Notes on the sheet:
Pot headers (bottom half, 1:1 with the mating board)
Switch headers and DC (top half)
Footswitch jack (3.5 mm TRS, PCB mounted)
Toggles (bat up closes 2-3, C&K 7000 convention)
Pots (Alps RK09L dual 10k lin, CW = pins 3 / 6, centre detent)
Power flags
